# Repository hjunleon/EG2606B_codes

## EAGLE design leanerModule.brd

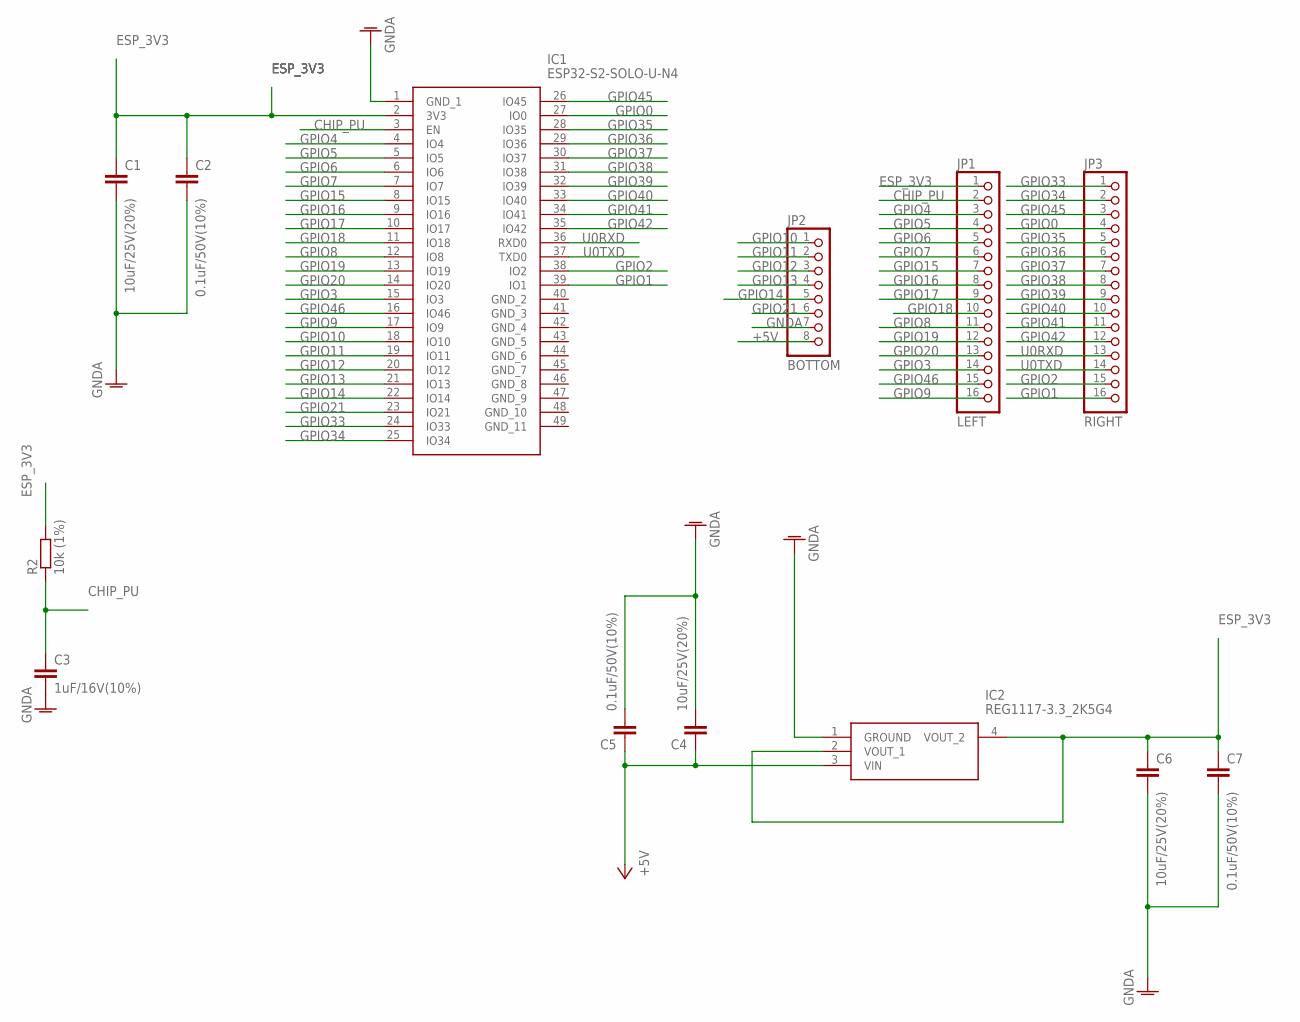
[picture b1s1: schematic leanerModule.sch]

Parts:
C1, C4, C6: 10uF/25V(20%); C0805
C2, C5, C7: 0.1uF/50V(10%); C0805
C3: 1uF/16V(10%); C0805
IC1: ESP32-S2-SOLO-U-N4; ESP32S2SOLOUN4
IC2: REG1117-3.3_2K5G4; SOT230P700X180-4N
JP1: LEFT; 1X16
JP2: BOTTOM; 1X08
JP3: RIGHT; 1X16
R2: 10k (1%); R0603

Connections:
+5V: C4.1, C5.1, IC2.3 (VIN), JP2.8
CHIP_PU: C3.1, IC1.3 (EN), JP1.2, R2.1
ESP_3V3: C1.1, C2.1, C6.1, C7.1, IC1.2 (3V3), IC2.2 (VOUT_1), IC2.4 (VOUT_2), JP1.1, R2.2
GNDA: C1.2, C2.2, C3.2, C4.2, C5.2, C6.2, C7.2, IC1.1 (GND_1), IC2.1 (GROUND), JP2.7
GPIO0: IC1.27 (IO0), JP3.4
GPIO1: IC1.39 (IO1), JP3.16
GPIO2: IC1.38 (IO2), JP3.15
GPIO3: IC1.15 (IO3), JP1.14
GPIO4: IC1.4 (IO4), JP1.3
GPIO5: IC1.5 (IO5), JP1.4
GPIO6: IC1.6 (IO6), JP1.5
GPIO7: IC1.7 (IO7), JP1.6
GPIO8: IC1.12 (IO8), JP1.11
GPIO9: IC1.17 (IO9), JP1.16
GPIO10: IC1.18 (IO10), JP2.1
GPIO11: IC1.19 (IO11), JP2.2
GPIO12: IC1.20 (IO12), JP2.3
GPIO13: IC1.21 (IO13), JP2.4
GPIO14: IC1.22 (IO14), JP2.5
GPIO15: IC1.8 (IO15), JP1.7
GPIO16: IC1.9 (IO16), JP1.8
GPIO17: IC1.10 (IO17), JP1.9
GPIO18: IC1.11 (IO18), JP1.10
GPIO19: IC1.13 (IO19), JP1.12
GPIO20: IC1.14 (IO20), JP1.13
GPIO21: IC1.23 (IO21), JP2.6
GPIO33: IC1.24 (IO33), JP3.1
GPIO34: IC1.25 (IO34), JP3.2
GPIO35: IC1.28 (IO35), JP3.5
GPIO36: IC1.29 (IO36), JP3.6
GPIO37: IC1.30 (IO37), JP3.7
GPIO38: IC1.31 (IO38), JP3.8
GPIO39: IC1.32 (IO39), JP3.9
GPIO40: IC1.33 (IO40), JP3.10
GPIO41: IC1.34 (IO41), JP3.11
GPIO42: IC1.35 (IO42), JP3.12
GPIO45: IC1.26 (IO45), JP3.3
GPIO46: IC1.16 (IO46), JP1.15
U0RXD: IC1.36 (RXD0), JP3.13
U0TXD: IC1.37 (TXD0), JP3.14

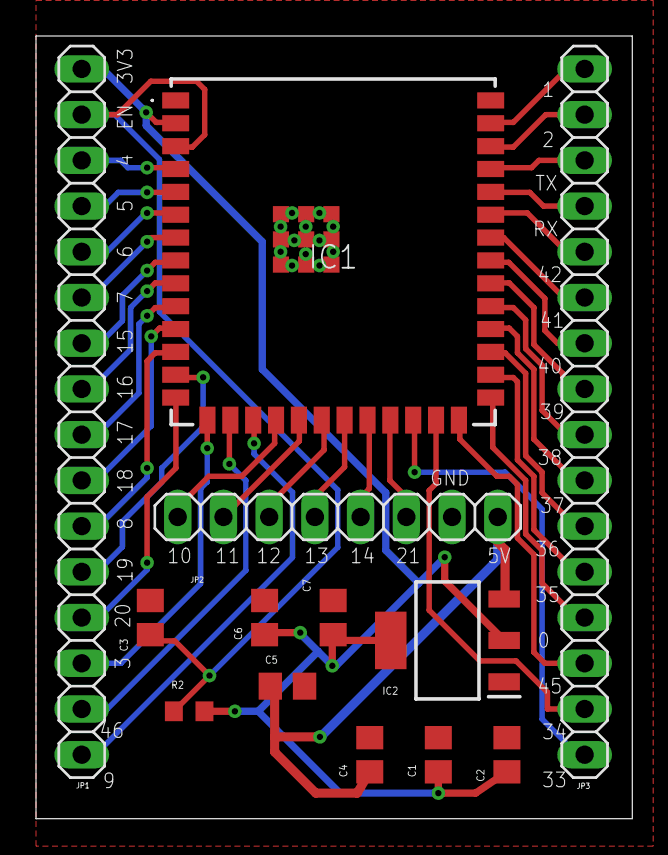
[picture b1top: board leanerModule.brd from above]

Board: 2 copper layers, 33.1 x 43.5 mm, 13 parts (0 on the bottom side), 40 nets.

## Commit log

2023-04-20 Hardware files
